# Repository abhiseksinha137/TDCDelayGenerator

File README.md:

# TDCDelayGenerator

This set of programs are used to control a VMI (Velocity Map Imaging) experiment.
## The Experiment

 Two optical elements are used in the experiment.
 1. An SPP (Spiral Phase Plate)
 2. A QWP (QWP)
 **Data Acquisition:**
 3. The TOF and position data from MCP are collected from a TDC in the form of a list mode file (lmf).

## Problem Statement
At each position of the SPP and QWP, the TDC data is acquired for an extended period of time (2-3 hours). Small changes in the laser beam due to changes in power or minute alignment changes can effect the individual runs leading to artifacts in the acquired data.

## Solution

 - The data will be acquired at each position for small duration (~ 3-5 min) for several runs. 
 - The same TDC acquisition file (lmf) will continue throughout the runs. 
 - A delay channel in the TDC is dedicated to distinguish the different parameters of the runs.
 
##  The Circuit
Delay Generator Chip **DS1023-25**
Stepper Motor Chip  **A4988**
A servo motor.
Piezo Rotation Stage :[ **CONEX-AG-PR100P**](https://www.newport.com/f/agilis-piezo-rotation-stages-with-conex-controller)
The circuit is detailed in the directory *./Circuit Details/*

## Circuit Control 
The various components of the circuit are controlled using a microcontroller (Arduino Nano) except for the piezo stage. 
The Arduino Nano code is in the directory *./Nanosecond_Delay_Generator_Circuit_Arduino_Code/delayGen5/delayGen5/*

## Overlord Code
A C# windows forms script is used to control all the elements (circuit elements via arduino) and conducting the Experiment.

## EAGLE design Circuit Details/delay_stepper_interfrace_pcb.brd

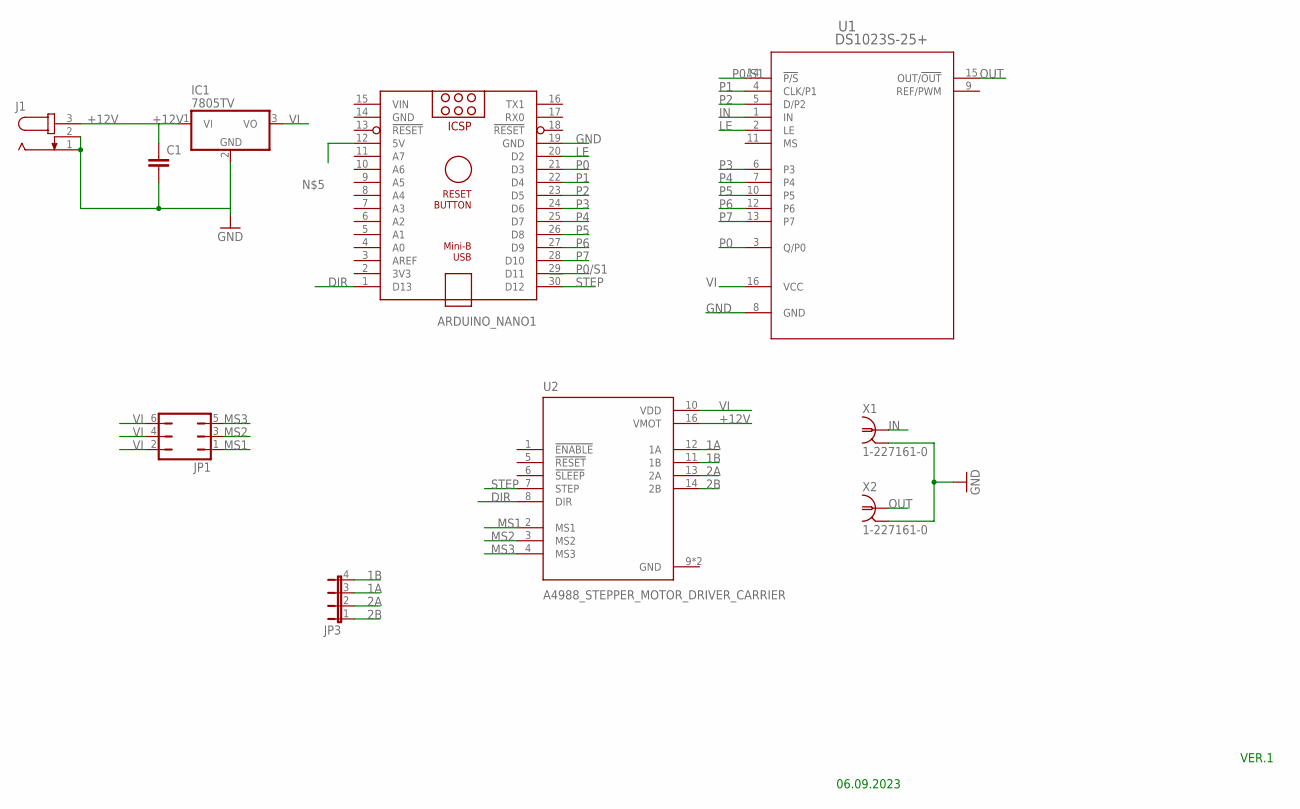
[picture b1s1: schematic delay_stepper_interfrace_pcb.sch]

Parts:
ARDUINO_NANO1: ARDUINO_NANO
C1: C2,5-3; C2.5-3
IC1: 7805TV; TO220V
J1: JACK-PLUG0; SPC4077
JP1: JP3Q
JP3: JP4E; JP4
U1: DS1023S-25+; 21-0042_AA_ADI
U2: A4988_STEPPER_MOTOR_DRIVER_CARRIER; MODULE_A4988_STEPPER_MOTOR_DRIVER_CARRIER
X1, X2: 1-227161-0; AMP_227161

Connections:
1A: JP3.3, U2.12 (1A)
1B: JP3.4, U2.11 (1B)
2A: JP3.2, U2.13 (2A)
2B: JP3.1, U2.14 (2B)
+12V: C1.1, IC1.1 (VI), J1.3, U2.16 (VMOT)
DIR: ARDUINO_NANO1.1 (D13), U2.8 (DIR)
GND: ARDUINO_NANO1.14 (GND), ARDUINO_NANO1.19 (GND), C1.2, IC1.2 (GND), J1.1, J1.2, U1.8 (GND), U2.9 (GND), U2.15 (GND), X1.2, X2.2
IN: U1.1 (IN), X1.1
LE: ARDUINO_NANO1.20 (D2), U1.2 (LE)
MS1: JP1.1, U2.2 (MS1)
MS2: JP1.3, U2.3 (MS2)
MS3: JP1.5, U2.4 (MS3)
OUT: U1.15 (OUT/!OUT), X2.1
P0: ARDUINO_NANO1.21 (D3), U1.3 (Q/P0)
P0/S1: ARDUINO_NANO1.29 (D11), U1.14 (!P/S)
P1: ARDUINO_NANO1.22 (D4), U1.4 (CLK/P1)
P2: ARDUINO_NANO1.23 (D5), U1.5 (D/P2)
P3: ARDUINO_NANO1.24 (D6), U1.6 (P3)
P4: ARDUINO_NANO1.25 (D7), U1.7 (P4)
P5: ARDUINO_NANO1.26 (D8), U1.10 (P5)
P6: ARDUINO_NANO1.27 (D9), U1.12 (P6)
P7: ARDUINO_NANO1.28 (D10), U1.13 (P7)
STEP: ARDUINO_NANO1.30 (D12), U2.7 (STEP)
VI: IC1.3 (VO), JP1.2, JP1.4, JP1.6, U1.16 (VCC), U2.10 (VDD)
VIN: ARDUINO_NANO1.15 (VIN)

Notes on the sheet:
06.09.2023
VER.1

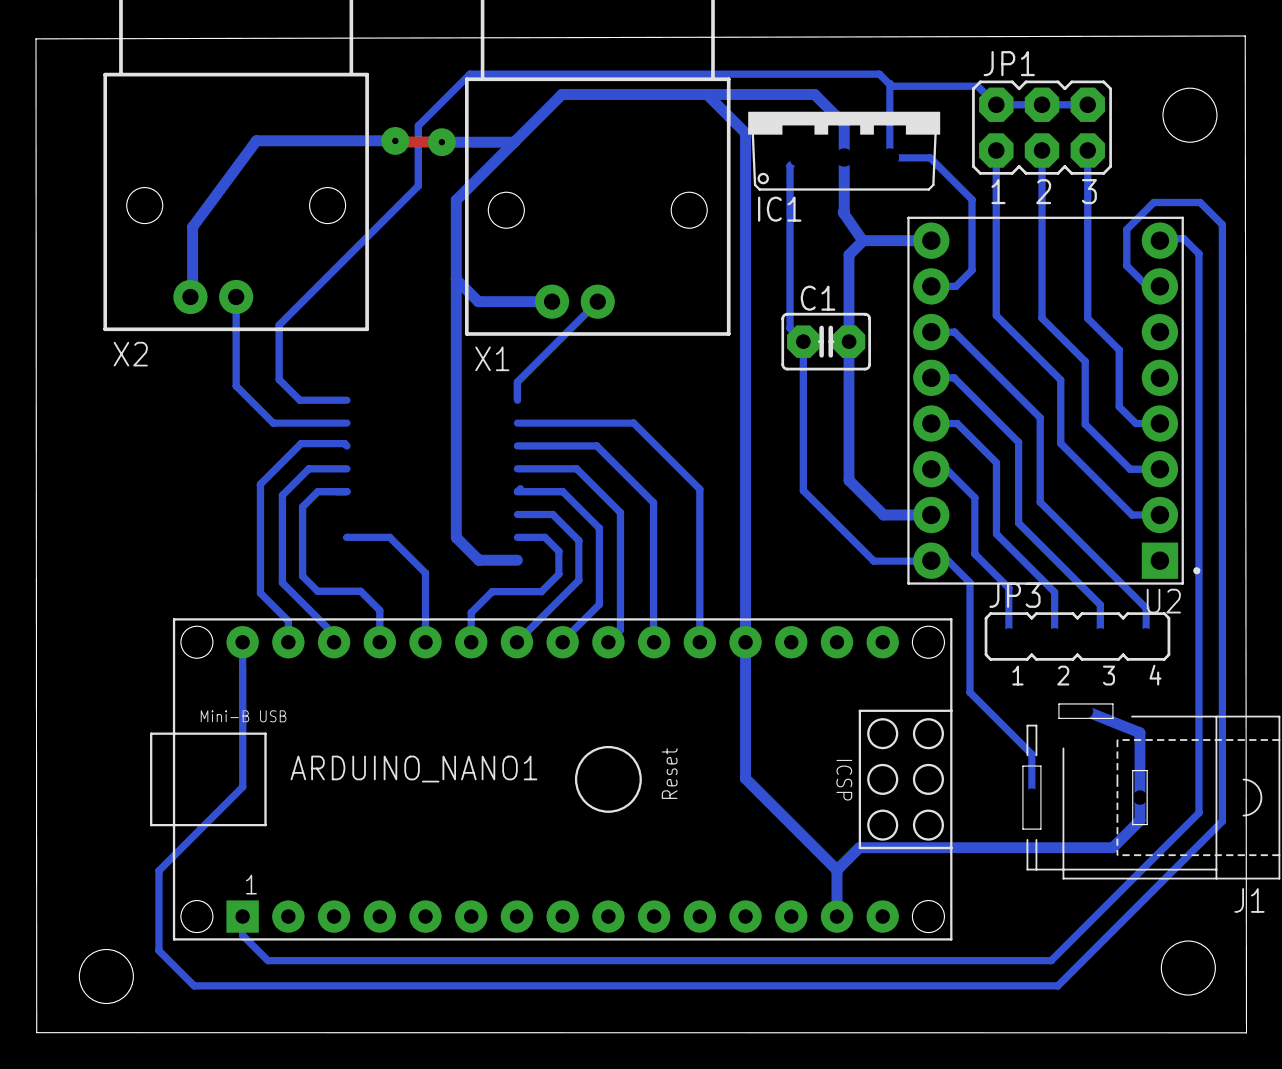
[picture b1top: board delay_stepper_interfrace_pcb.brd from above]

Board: 2 copper layers, 67.2 x 55.4 mm, 10 parts (1 on the bottom side), 24 nets.

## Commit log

2023-09-18 Added arduino code for delay value response. C# code updated.
2023-09-20 Added completion Notification
2023-10-03 Conex Agilis
2023-10-03 error corrected
2023-10-06 Debug Files
2023-10-06 Max Delay Changed to 190
2023-10-16 Removed bug from rounding errors
2023-10-16 Removed Bug of Rounding to Floor
2023-10-16 SerialPort.DiscardInBuffer issue resolved
2023-10-17 Added delayGen5.ino; syncrhonised stage motion using AutoResetEvent
2023-10-18 AutoResetEvent in all nano calls within bckWrkr
2023-10-18 Replaced Sleep with Stopwatch
2023-10-18 Added debugging lines
    To see what commands are sent
2023-10-18 Changes in Arduino
2023-10-18 Working + Arduino Changes
2023-10-19 Added readme file

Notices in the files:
parts and their libraries:
COPYRIGHT: Copyright (C) 2023 Ultra Librarian. All rights reserved.
